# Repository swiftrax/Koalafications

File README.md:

# Koalafications

75% Stacked Acrylic Keyboard with an OLED screen. QMK/VIA compatible 

## Hardware

* M3 Hex Spacer 10mm x 8
* M3 Hex Spacer 6mm x 3
* M3 Screw 8mm x 19
* M3 Screw 6mm x 3

## License

This repository is under the [CC0 1.0 Universal License](https://github.com/swiftrax/Nodu/blob/main/LICENSE). If you plan to sell these pcbs, make sure to read it.

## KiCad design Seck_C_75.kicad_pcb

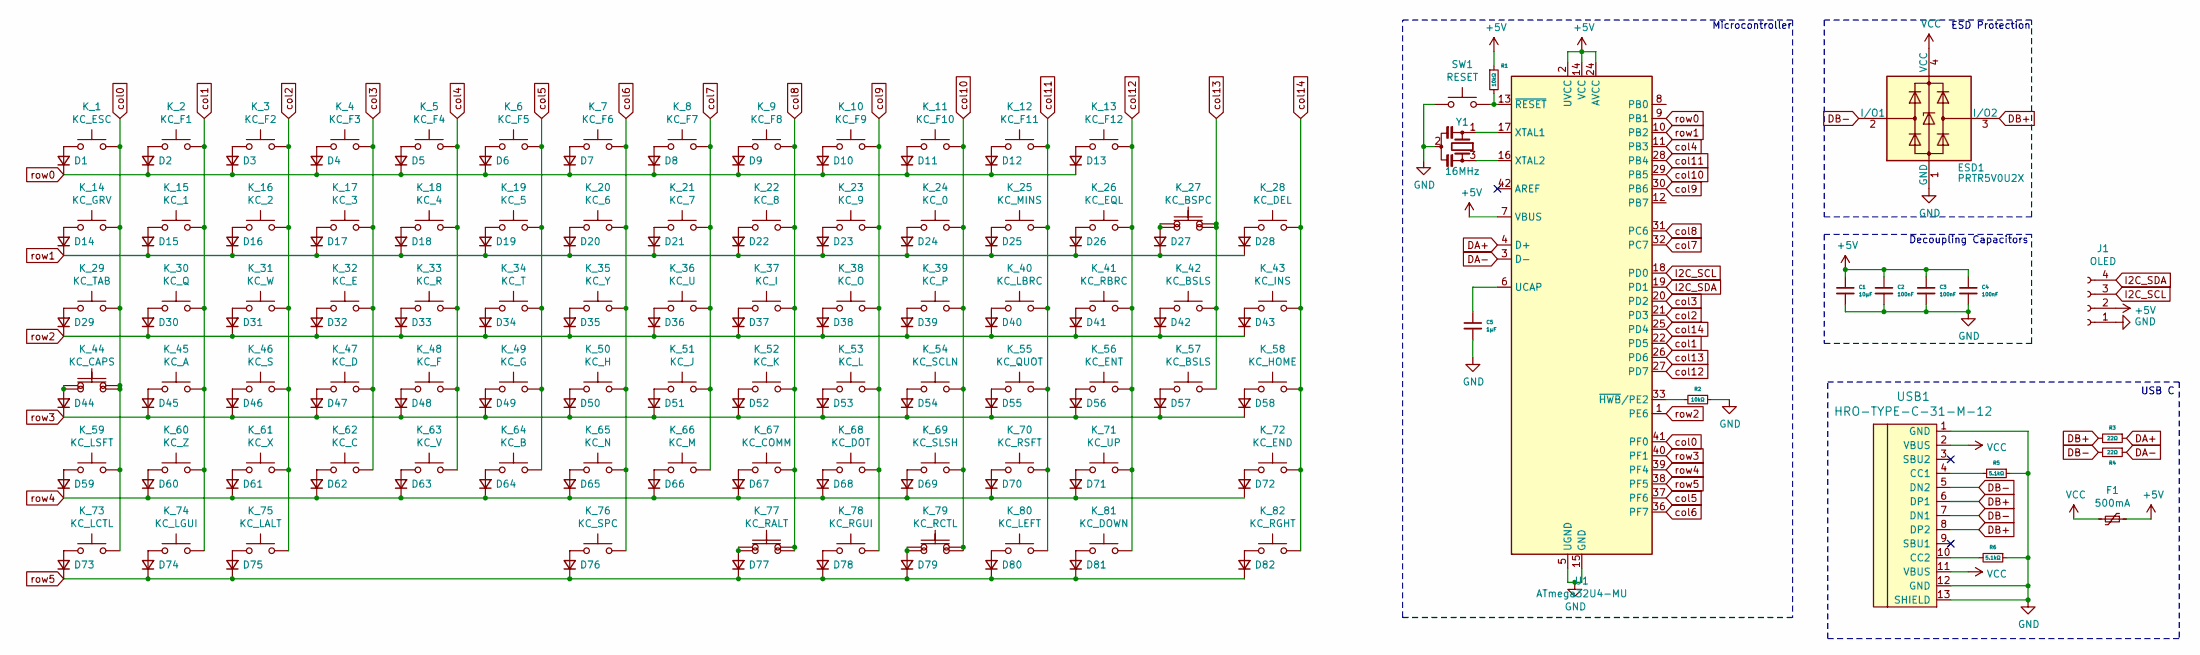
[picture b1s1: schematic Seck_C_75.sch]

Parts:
C1: 10µF; C_0603_Annotated
C2, C3, C4: 100nF; C_0603_Annotated
C5: 1µF; C_0603_Annotated
D1, D2, D3, D4, D5, D6, D7, D8, D9, D10, D11, D12, D13, D14, D15, D16, D17, D18, D19, D20, D21, D22, D23, D24, D25, D26, D27, D28, D29, D30, D31, D32, D33, D34, D35, D36, D37, D38, D39, D40, D41, D42, D43, D44, D45, D46, D47, D48, D49, D50, D51, D52, D53, D54, D55, D56, D57, D58, D59, D60, D61, D62, D63, D64, D65, D66, D67, D68, D69, D70, D71, D72, D73, D74, D75, D76, D77, D78, D79, D80, D81, D82: D_Small; D_0603_1608Metric_Pad1.05x0.95mm_HandSolder
ESD1: PRTR5V0U2X; SOT-143
F1: 500mA; Fuse_1206_Annotated
J1: OLED; SSD1306_OLED
K_1: KC_ESC; MXOnly-1U-NoLED
K_2: KC_F1; MXOnly-1U-NoLED
K_3: KC_F2; MXOnly-1U-NoLED
K_4: KC_F3; MXOnly-1U-NoLED
K_5: KC_F4; MXOnly-1U-NoLED
K_6: KC_F5; MXOnly-1U-NoLED
K_7: KC_F6; MXOnly-1U-NoLED
K_8: KC_F7; MXOnly-1U-NoLED
K_9: KC_F8; MXOnly-1U-NoLED
K_10: KC_F9; MXOnly-1U-NoLED
K_11: KC_F10; MXOnly-1U-NoLED
K_12: KC_F11; MXOnly-1U-NoLED
K_13: KC_F12; MXOnly-1U-NoLED
K_14: KC_GRV; MXOnly-1U-NoLED
K_15: KC_1; MXOnly-1U-NoLED
K_16: KC_2; MXOnly-1U-NoLED
K_17: KC_3; MXOnly-1U-NoLED
K_18: KC_4; MXOnly-1U-NoLED
K_19: KC_5; MXOnly-1U-NoLED
K_20: KC_6; MXOnly-1U-NoLED
K_21: KC_7; MXOnly-1U-NoLED
K_22: KC_8; MXOnly-1U-NoLED
K_23: KC_9; MXOnly-1U-NoLED
K_24: KC_0; MXOnly-1U-NoLED
K_25: KC_MINS; MXOnly-1U-NoLED
K_26: KC_EQL; MXOnly-1U-NoLED
K_27: KC_BSPC; MXOnly-2U-NoLED
K_28: KC_DEL; MXOnly-1U-NoLED
K_29: KC_TAB; MXOnly-1.5U-NoLED
K_30: KC_Q; MXOnly-1U-NoLED
K_31: KC_W; MXOnly-1U-NoLED
K_32: KC_E; MXOnly-1U-NoLED
K_33: KC_R; MXOnly-1U-NoLED
K_34: KC_T; MXOnly-1U-NoLED
K_35: KC_Y; MXOnly-1U-NoLED
K_36: KC_U; MXOnly-1U-NoLED
K_37: KC_I; MXOnly-1U-NoLED
K_38: KC_O; MXOnly-1U-NoLED
K_39: KC_P; MXOnly-1U-NoLED
K_40: KC_LBRC; MXOnly-1U-NoLED
K_41: KC_RBRC; MXOnly-1U-NoLED
K_42: KC_BSLS; MXOnly-1.5U-NoLED
K_43: KC_INS; MXOnly-1U-NoLED
K_44: KC_CAPS; MXOnly-1.75U-NoLED
K_45: KC_A; MXOnly-1U-NoLED
K_46: KC_S; MXOnly-1U-NoLED
K_47: KC_D; MXOnly-1U-NoLED
K_48: KC_F; MXOnly-1U-NoLED
K_49: KC_G; MXOnly-1U-NoLED
K_50: KC_H; MXOnly-1U-NoLED
K_51: KC_J; MXOnly-1U-NoLED
K_52: KC_K; MXOnly-1U-NoLED
K_53: KC_L; MXOnly-1U-NoLED
K_54: KC_SCLN; MXOnly-1U-NoLED
K_55: KC_QUOT; MXOnly-1U-NoLED
K_56: KC_ENT; MXOnly-2.25U-NoLED
K_57: KC_BSLS; MXOnly-1U-NoLED
K_58: KC_HOME; MXOnly-1U-NoLED
K_59: KC_LSFT; MXOnly-2.25U-NoLED
K_60: KC_Z; MXOnly-1U-NoLED
K_61: KC_X; MXOnly-1U-NoLED
K_62: KC_C; MXOnly-1U-NoLED
K_63: KC_V; MXOnly-1U-NoLED
K_64: KC_B; MXOnly-1U-NoLED
K_65: KC_N; MXOnly-1U-NoLED
K_66: KC_M; MXOnly-1U-NoLED
K_67: KC_COMM; MXOnly-1U-NoLED
K_68: KC_DOT; MXOnly-1U-NoLED
K_69: KC_SLSH; MXOnly-1U-NoLED
K_70: KC_RSFT; MXOnly-1.75U-NoLED
K_71: KC_UP; MXOnly-1U-NoLED
K_72: KC_END; MXOnly-1U-NoLED
K_73: KC_LCTL; MXOnly-1.25U-NoLED
K_74: KC_LGUI; MXOnly-1.25U-NoLED
K_75: KC_LALT; MXOnly-1.25U-NoLED
K_76: KC_SPC; MXOnly-6.25U-ReversedStabilizers-NoLED
K_77: KC_RALT; MXOnly-1U-NoLED
K_78: KC_RGUI; MXOnly-1U-NoLED
K_79: KC_RCTL; MXOnly-1U-NoLED
K_80: KC_LEFT; MXOnly-1U-NoLED
K_81: KC_DOWN; MXOnly-1U-NoLED
K_82: KC_RGHT; MXOnly-1U-NoLED
K_113A1: KC_BSPC; MXOnly-1U-NoLED
K_300A1: KC_CAPS; MXOnly-1.25U-NoLED
K_508A1: KC_; MXOnly-1.5U-NoLED
K_510A1: KC_RCTL; MXOnly-1.5U-NoLED
R1, R2: 10kΩ; R_0603_Annotated
R3, R4: 22Ω; R_0603_Annotated
R5, R6: 5.1kΩ; R_0603_Annotated
SW1: RESET; RESET_PADS
U1: ATmega32U4-MU; QFN-44-1EP_7x7mm_P0.5mm_EP5.2x5.2mm
USB1: HRO-TYPE-C-31-M-12
Y1: 16MHz; Resonator_3Pin_Annotated

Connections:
+5V: C1.1, C2.1, C3.1, C4.1, F1.1, J1.2, R1.1, U1.2 (UVCC), U1.7 (VBUS), U1.14 (VCC), U1.24 (AVCC), U1.34 (VCC), U1.44 (AVCC)
DA+: R3.1, U1.4 (D+)
DA-: R4.1, U1.3 (D-)
DB+: ESD1.3 (I/O2), R3.2, USB1.6 (DP1), USB1.8 (DP2)
DB-: ESD1.2 (I/O1), R4.2, USB1.5 (DN2), USB1.7 (DN1)
GND: C1.2, C2.2, C3.2, C4.2, C5.2, ESD1.1 (GND), J1.1, R2.1, R5.1, R6.1, SW1.1, U1.5 (UGND), U1.15 (GND), U1.23 (GND), U1.35 (GND), U1.43 (GND), U1.45 (GND), USB1.1 (GND), USB1.12 (GND), USB1.13 (SHIELD), Y1.2
I2C_SCL: J1.3, U1.18 (PD0)
I2C_SDA: J1.4, U1.19 (PD1)
unnamed: C5.1, U1.6 (UCAP)
unnamed: D1.2 (A), K_1.1
unnamed: D2.2 (A), K_2.1
unnamed: D3.2 (A), K_3.1
unnamed: D4.2 (A), K_4.1
unnamed: D5.2 (A), K_5.1
unnamed: D6.2 (A), K_6.1
unnamed: D7.2 (A), K_7.1
unnamed: D8.2 (A), K_8.1
unnamed: D9.2 (A), K_9.1
unnamed: D10.2 (A), K_10.1
unnamed: D11.2 (A), K_11.1
unnamed: D12.2 (A), K_12.1
unnamed: D13.2 (A), K_13.1
unnamed: D14.2 (A), K_14.1
unnamed: D15.2 (A), K_15.1
unnamed: D16.2 (A), K_16.1
unnamed: D17.2 (A), K_17.1
unnamed: D18.2 (A), K_18.1
unnamed: D19.2 (A), K_19.1
unnamed: D20.2 (A), K_20.1
unnamed: D21.2 (A), K_21.1
unnamed: D22.2 (A), K_22.1
unnamed: D23.2 (A), K_23.1
unnamed: D24.2 (A), K_24.1
unnamed: D25.2 (A), K_25.1
unnamed: D26.2 (A), K_26.1
unnamed: D27.2 (A), K_27.1, K_113A1.1
unnamed: D28.2 (A), K_28.1
unnamed: D29.2 (A), K_29.1
unnamed: D30.2 (A), K_30.1
unnamed: D31.2 (A), K_31.1
unnamed: D32.2 (A), K_32.1
unnamed: D33.2 (A), K_33.1
unnamed: D34.2 (A), K_34.1
unnamed: D35.2 (A), K_35.1
unnamed: D36.2 (A), K_36.1
unnamed: D37.2 (A), K_37.1
unnamed: D38.2 (A), K_38.1
unnamed: D39.2 (A), K_39.1
unnamed: D40.2 (A), K_40.1
unnamed: D41.2 (A), K_41.1
unnamed: D42.2 (A), K_42.1
unnamed: D43.2 (A), K_43.1
unnamed: D44.2 (A), K_44.1, K_300A1.1
unnamed: D45.2 (A), K_45.1
unnamed: D46.2 (A), K_46.1
unnamed: D47.2 (A), K_47.1
unnamed: D48.2 (A), K_48.1
unnamed: D49.2 (A), K_49.1
unnamed: D50.2 (A), K_50.1
unnamed: D51.2 (A), K_51.1
unnamed: D52.2 (A), K_52.1
unnamed: D53.2 (A), K_53.1
unnamed: D54.2 (A), K_54.1
unnamed: D55.2 (A), K_55.1
unnamed: D56.2 (A), K_56.1
unnamed: D57.2 (A), K_57.1
unnamed: D58.2 (A), K_58.1
unnamed: D59.2 (A), K_59.1
unnamed: D60.2 (A), K_60.1
unnamed: D61.2 (A), K_61.1
unnamed: D62.2 (A), K_62.1
unnamed: D63.2 (A), K_63.1
unnamed: D64.2 (A), K_64.1
unnamed: D65.2 (A), K_65.1
unnamed: D66.2 (A), K_66.1
unnamed: D67.2 (A), K_67.1
unnamed: D68.2 (A), K_68.1
unnamed: D69.2 (A), K_69.1
unnamed: D70.2 (A), K_70.1
unnamed: D71.2 (A), K_71.1
unnamed: D72.2 (A), K_72.1
unnamed: D73.2 (A), K_73.1
unnamed: D74.2 (A), K_74.1
unnamed: D75.2 (A), K_75.1
unnamed: D76.2 (A), K_76.1
unnamed: D77.2 (A), K_77.1, K_508A1.1
unnamed: D78.2 (A), K_78.1
unnamed: D79.2 (A), K_79.1, K_510A1.1
unnamed: D80.2 (A), K_80.1
unnamed: D81.2 (A), K_81.1
unnamed: D82.2 (A), K_82.1
unnamed: R1.2, SW1.2, U1.13 (~RESET)
unnamed: R2.2, U1.33 (~HWB~/PE2)
unnamed: R5.2, USB1.4 (CC1)
unnamed: R6.2, USB1.10 (CC2)
unnamed: U1.16 (XTAL2), Y1.3
unnamed: U1.17 (XTAL1), Y1.1
VCC: ESD1.4 (VCC), F1.2, USB1.2 (VBUS), USB1.11 (VBUS)
col0: K_1.2, K_14.2, K_29.2, K_44.2, K_59.2, K_73.2, K_300A1.2, U1.41 (PF0)
col1: K_2.2, K_15.2, K_30.2, K_45.2, K_60.2, K_74.2, U1.22 (PD5)
col2: K_3.2, K_16.2, K_31.2, K_46.2, K_61.2, K_75.2, U1.21 (PD3)
col3: K_4.2, K_17.2, K_32.2, K_47.2, K_62.2, U1.20 (PD2)
col4: K_5.2, K_18.2, K_33.2, K_48.2, K_63.2, U1.11 (PB3)
col5: K_6.2, K_19.2, K_34.2, K_49.2, K_64.2, U1.37 (PF6)
col6: K_7.2, K_20.2, K_35.2, K_50.2, K_65.2, K_76.2, U1.36 (PF7)
col7: K_8.2, K_21.2, K_36.2, K_51.2, K_66.2, U1.32 (PC7)
col8: K_9.2, K_22.2, K_37.2, K_52.2, K_67.2, K_77.2, K_508A1.2, U1.31 (PC6)
col9: K_10.2, K_23.2, K_38.2, K_53.2, K_68.2, K_78.2, U1.30 (PB6)
col10: K_11.2, K_24.2, K_39.2, K_54.2, K_69.2, K_79.2, K_510A1.2, U1.29 (PB5)
col11: K_12.2, K_25.2, K_40.2, K_55.2, K_70.2, K_80.2, U1.28 (PB4)
col12: K_13.2, K_26.2, K_41.2, K_56.2, K_71.2, K_81.2, U1.27 (PD7)
col13: K_27.2, K_42.2, K_57.2, K_113A1.2, U1.26 (PD6)
col14: K_28.2, K_43.2, K_58.2, K_72.2, K_82.2, U1.25 (PD4)
row0: D1.1 (K), D2.1 (K), D3.1 (K), D4.1 (K), D5.1 (K), D6.1 (K), D7.1 (K), D8.1 (K), D9.1 (K), D10.1 (K), D11.1 (K), D12.1 (K), D13.1 (K), U1.9 (PB1)
row1: D14.1 (K), D15.1 (K), D16.1 (K), D17.1 (K), D18.1 (K), D19.1 (K), D20.1 (K), D21.1 (K), D22.1 (K), D23.1 (K), D24.1 (K), D25.1 (K), D26.1 (K), D27.1 (K), D28.1 (K), U1.10 (PB2)
row2: D29.1 (K), D30.1 (K), D31.1 (K), D32.1 (K), D33.1 (K), D34.1 (K), D35.1 (K), D36.1 (K), D37.1 (K), D38.1 (K), D39.1 (K), D40.1 (K), D41.1 (K), D42.1 (K), D43.1 (K), U1.1 (PE6)
row3: D44.1 (K), D45.1 (K), D46.1 (K), D47.1 (K), D48.1 (K), D49.1 (K), D50.1 (K), D51.1 (K), D52.1 (K), D53.1 (K), D54.1 (K), D55.1 (K), D56.1 (K), D57.1 (K), D58.1 (K), U1.40 (PF1)
row4: D59.1 (K), D60.1 (K), D61.1 (K), D62.1 (K), D63.1 (K), D64.1 (K), D65.1 (K), D66.1 (K), D67.1 (K), D68.1 (K), D69.1 (K), D70.1 (K), D71.1 (K), D72.1 (K), U1.39 (PF4)
row5: D73.1 (K), D74.1 (K), D75.1 (K), D76.1 (K), D77.1 (K), D78.1 (K), D79.1 (K), D80.1 (K), D81.1 (K), D82.1 (K), U1.38 (PF5)

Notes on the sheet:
Decoupling Capacitors
ESD Protection
Microcontroller
USB C

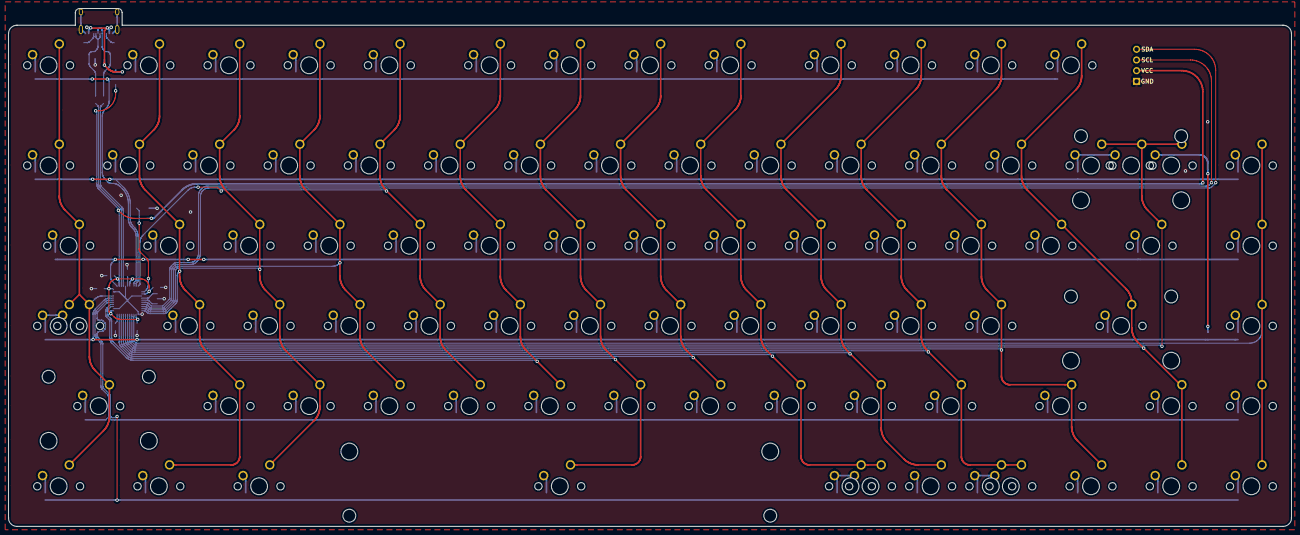
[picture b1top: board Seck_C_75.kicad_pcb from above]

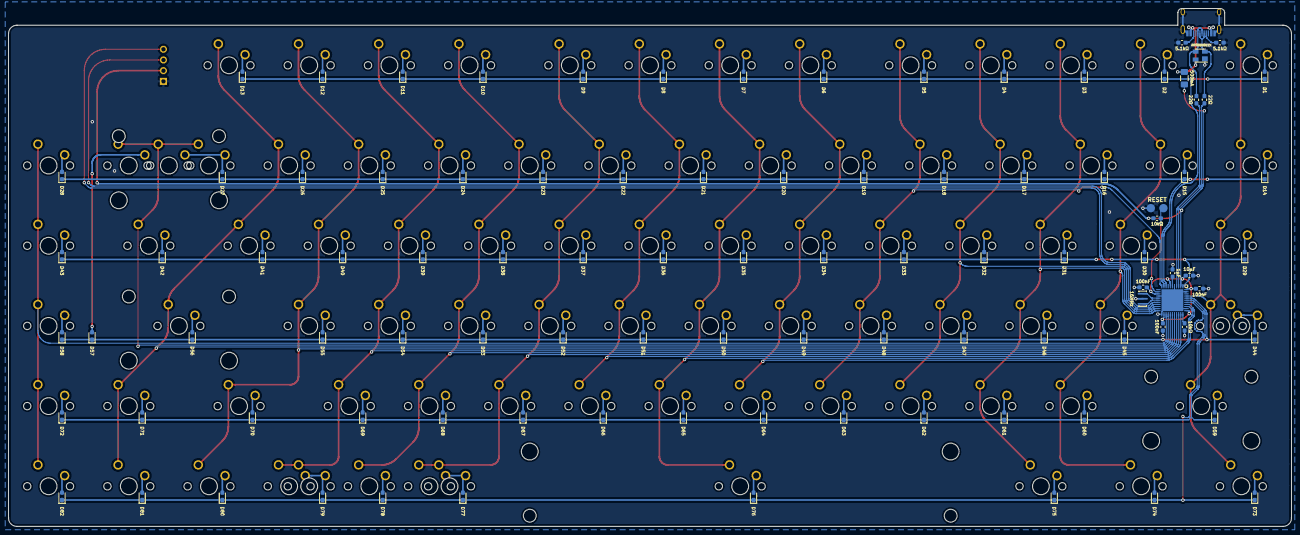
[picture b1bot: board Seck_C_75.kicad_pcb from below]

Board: 2 copper layers, 304.8 x 123.0 mm, 186 parts (99 on the bottom side), 119 nets.

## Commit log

2020-12-30 Init commit
2020-12-31 Layout
2020-12-31 Layout Diodes
2020-12-31 Layout Diodes + Route Cols
2021-01-02 Diodes
2021-01-06 Finish
2021-01-06 Make Gerbers + add Art
2021-01-07 Rename
2021-01-07 Organize
2021-01-07 Add illustrator files
2021-03-09 Create LICENSE
